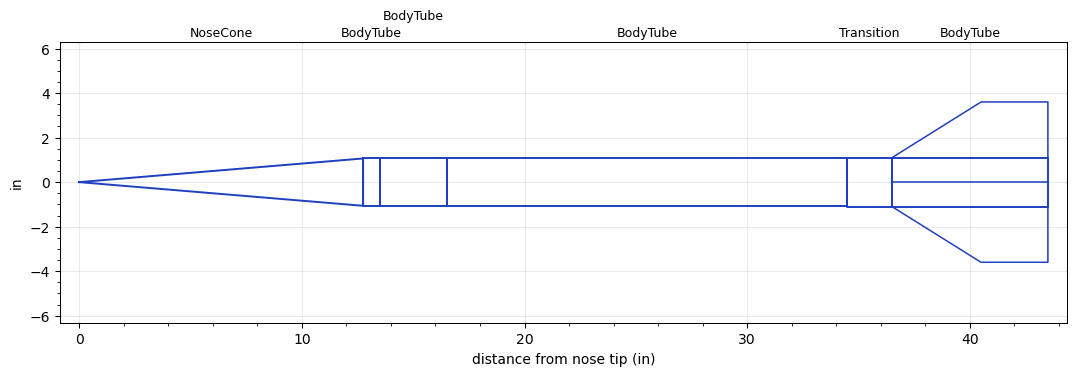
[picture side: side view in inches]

<RASAeroDocument>
 <FileVersion>2</FileVersion>
 <RocketDesign>
  <NoseCone>
   <Length>12.75</Length>
   <Diameter>2.125</Diameter>
   <Shape>Conical</Shape>
   <BluntRadius>0.08</BluntRadius>
   <Location>0</Location>
  </NoseCone>
  <BodyTube>
   <Length>0.75</Length>
   <Diameter>2.125</Diameter>
   <Location>12.75</Location>
  </BodyTube>
  <BodyTube>
   <Length>3</Length>
   <Diameter>2.125</Diameter>
   <Location>13.5</Location>
  </BodyTube>
  <BodyTube>
   <Length>18</Length>
   <Diameter>2.125</Diameter>
   <Location>16.5</Location>
  </BodyTube>
  <Transition>
   <Length>2</Length>
   <Diameter>2.2</Diameter>
   <Location>34.5</Location>
   <RearDiameter>2.2</RearDiameter>
  </Transition>
  <BodyTube>
   <Length>7</Length>
   <Diameter>2.2</Diameter>
   <Location>36.5</Location>
   <Fin>
    <Count>4</Count>
    <Chord>7</Chord>
    <Span>2.5</Span>
    <SweepDistance>4</SweepDistance>
    <TipChord>3</TipChord>
    <Thickness>0.125</Thickness>
    <LERadius>0.024</LERadius>
    <Location>7</Location>
    <AirfoilSection>Hexagonal</AirfoilSection>
    <FX1>0.5</FX1>
    <FX3>0.5</FX3>
   </Fin>
  </BodyTube>
  <Surface>Rough Camouflage Paint</Surface>
  <ModifiedBarrowman>True</ModifiedBarrowman>
  <Turbulence>True</Turbulence>
  <UseBooster1>False</UseBooster1>
  <UseBooster2>False</UseBooster2>
 </RocketDesign>
 <LaunchSite>
  <Altitude>0</Altitude>
  <Pressure>29.9214</Pressure>
  <RodAngle>0</RodAngle>
  <RodLength>71.9999</RodLength>
  <Temperature>59</Temperature>
  <WindSpeed>4.4739</WindSpeed>
 </LaunchSite>
 <Recovery>
  <Altitude1>0</Altitude1>
  <Altitude2>1000</Altitude2>
  <DeviceType1>Parachute</DeviceType1>
  <DeviceType2>Parachute</DeviceType2>
  <Event1>False</Event1>
  <Event2>False</Event2>
  <Size1>5</Size1>
  <Size2>25</Size2>
  <EventType1>Apogee</EventType1>
  <EventType2>Altitude</EventType2>
  <CD1>0.5</CD1>
  <CD2>0.8</CD2>
 </Recovery>
 <SimulationList>
  <Simulation>
   <SustainerEngine>L1049AB(NC)  (Polaris)</SustainerEngine>
   <SustainerLaunchWt>6.73</SustainerLaunchWt>
   <SustainerNozzleDiameter>2</SustainerNozzleDiameter>
   <SustainerCG>28.06</SustainerCG>
   <SustainerIgnitionDelay>0</SustainerIgnitionDelay>
   <Booster1SeparationDelay>0</Booster1SeparationDelay>
   <Booster1IgnitionDelay>0</Booster1IgnitionDelay>
   <IncludeBooster1>False</IncludeBooster1>
   <Booster2Delay>0</Booster2Delay>
   <IncludeBooster2>False</IncludeBooster2>
   <TimetoApogee>25.24048</TimetoApogee>
   <MaxAltitude>17717.1</MaxAltitude>
   <MaxVelocity>3009.094</MaxVelocity>
  </Simulation>
 </SimulationList>
</RASAeroDocument>
